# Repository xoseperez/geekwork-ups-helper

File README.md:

# GeekWorm UPS Helper

This repository contains the PCB design for an addon board for the Raspberry Pi + GeekWorm UPS Hat.

Check my blog post about this project to know more: http://tinkerman.cat/geekworm-power-pack-hat-hack/

## License

The PCB design and layout is licensed under CC-SA-BY-NC-4.0 International.

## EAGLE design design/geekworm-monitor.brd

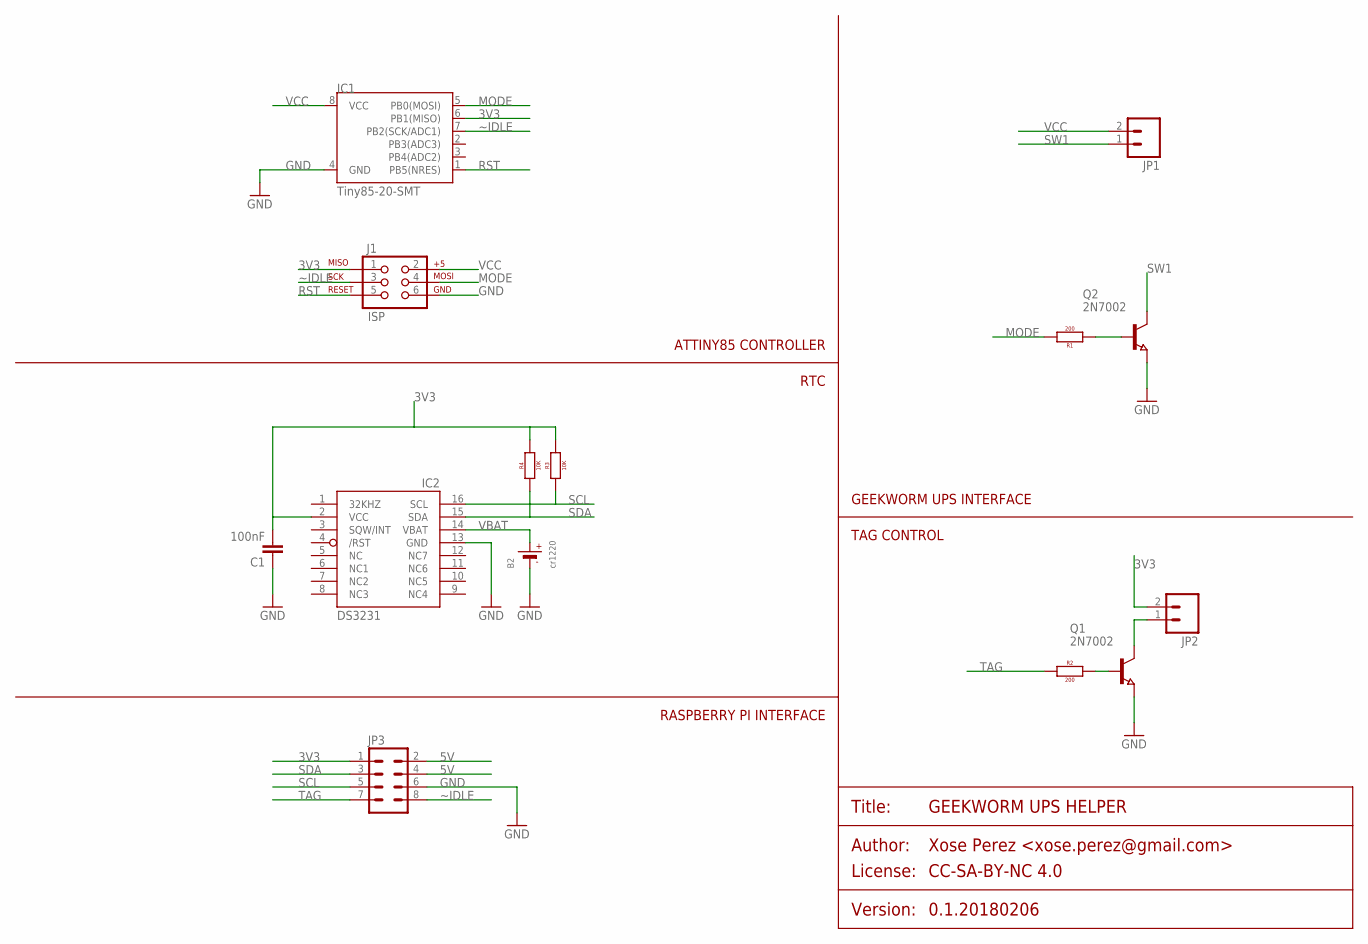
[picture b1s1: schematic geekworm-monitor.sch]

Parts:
B2: cr1220; MICROBUILDER_CR1220-2
C1: 100nF; 0805
IC1: Tiny85-20-SMT; SO08-EIAJ
IC2: DS3231/SO; SO16W
J1: ISP; 2X3EDGE
JP1, JP2: M02-JST-2MM-SMT; JST-2-SMD
JP3: M04X2; 2X4
Q1, Q2: 2N7002; SOT23
R1, R2: 200; 0805
R3, R4: 10K; 0805

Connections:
3V3: C1.2, IC1.6 (PB1(MISO)), IC2.2 (VCC), J1.1, JP2.2 (1), JP3.1, R3.2, R4.2
5V: JP3.2, JP3.4
GND: B2.-, C1.1, IC1.4 (GND), IC2.13 (GND), J1.6, JP3.6, Q1.2 (E), Q2.2 (E)
MODE: IC1.5 (PB0(MOSI)), J1.4, R1.2
unnamed: Q1.1 (B), R2.2
unnamed: Q2.1 (B), R1.1
unnamed: JP2.1 (2), Q1.3 (C)
RST: IC1.1 (PB5(NRES)), J1.5
SCL: IC2.16 (SCL), JP3.5, R3.1
SDA: IC2.15 (SDA), JP3.3, R4.1
SW1: JP1.1 (2), Q2.3 (C)
TAG: JP3.7, R2.1
VBAT: B2.+, IC2.14 (VBAT)
VCC: IC1.8 (VCC), J1.2, JP1.2 (1)
~IDLE: IC1.7 (PB2(SCK/ADC1)), J1.3, JP3.8

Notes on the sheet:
RASPBERRY PI INTERFACE
RTC
ATTINY85 CONTROLLER
GEEKWORM UPS INTERFACE
TAG CONTROL

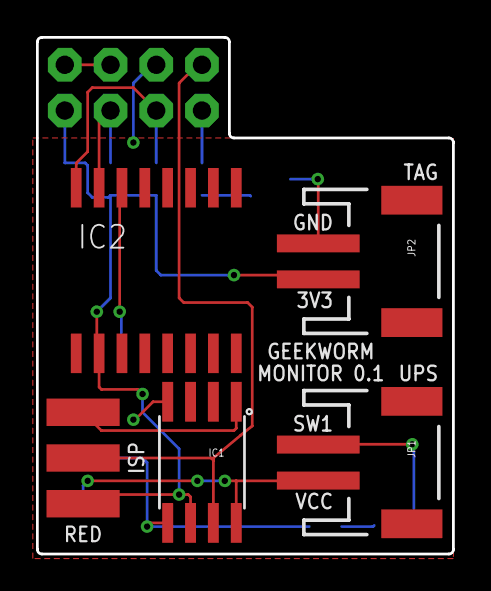
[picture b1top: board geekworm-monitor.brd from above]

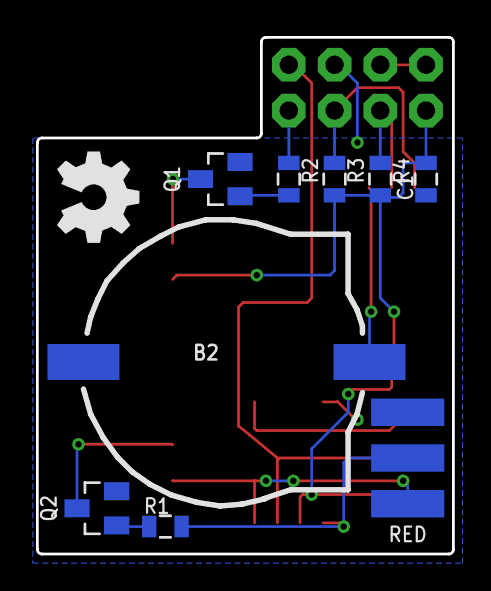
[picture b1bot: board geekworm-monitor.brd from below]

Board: 2 copper layers, 23.1 x 28.7 mm, 14 parts (8 on the bottom side), 15 nets.

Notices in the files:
design/geekworm-monitor.sch:
PROJECT_LICENSE: CC-SA-BY-NC 4.0
parts and their libraries:
SparkFun-DigitalIC: Licensing: Creative Commons ShareAlike 4.0 International - https://creativecommons.org/licenses/by-sa/4.0
